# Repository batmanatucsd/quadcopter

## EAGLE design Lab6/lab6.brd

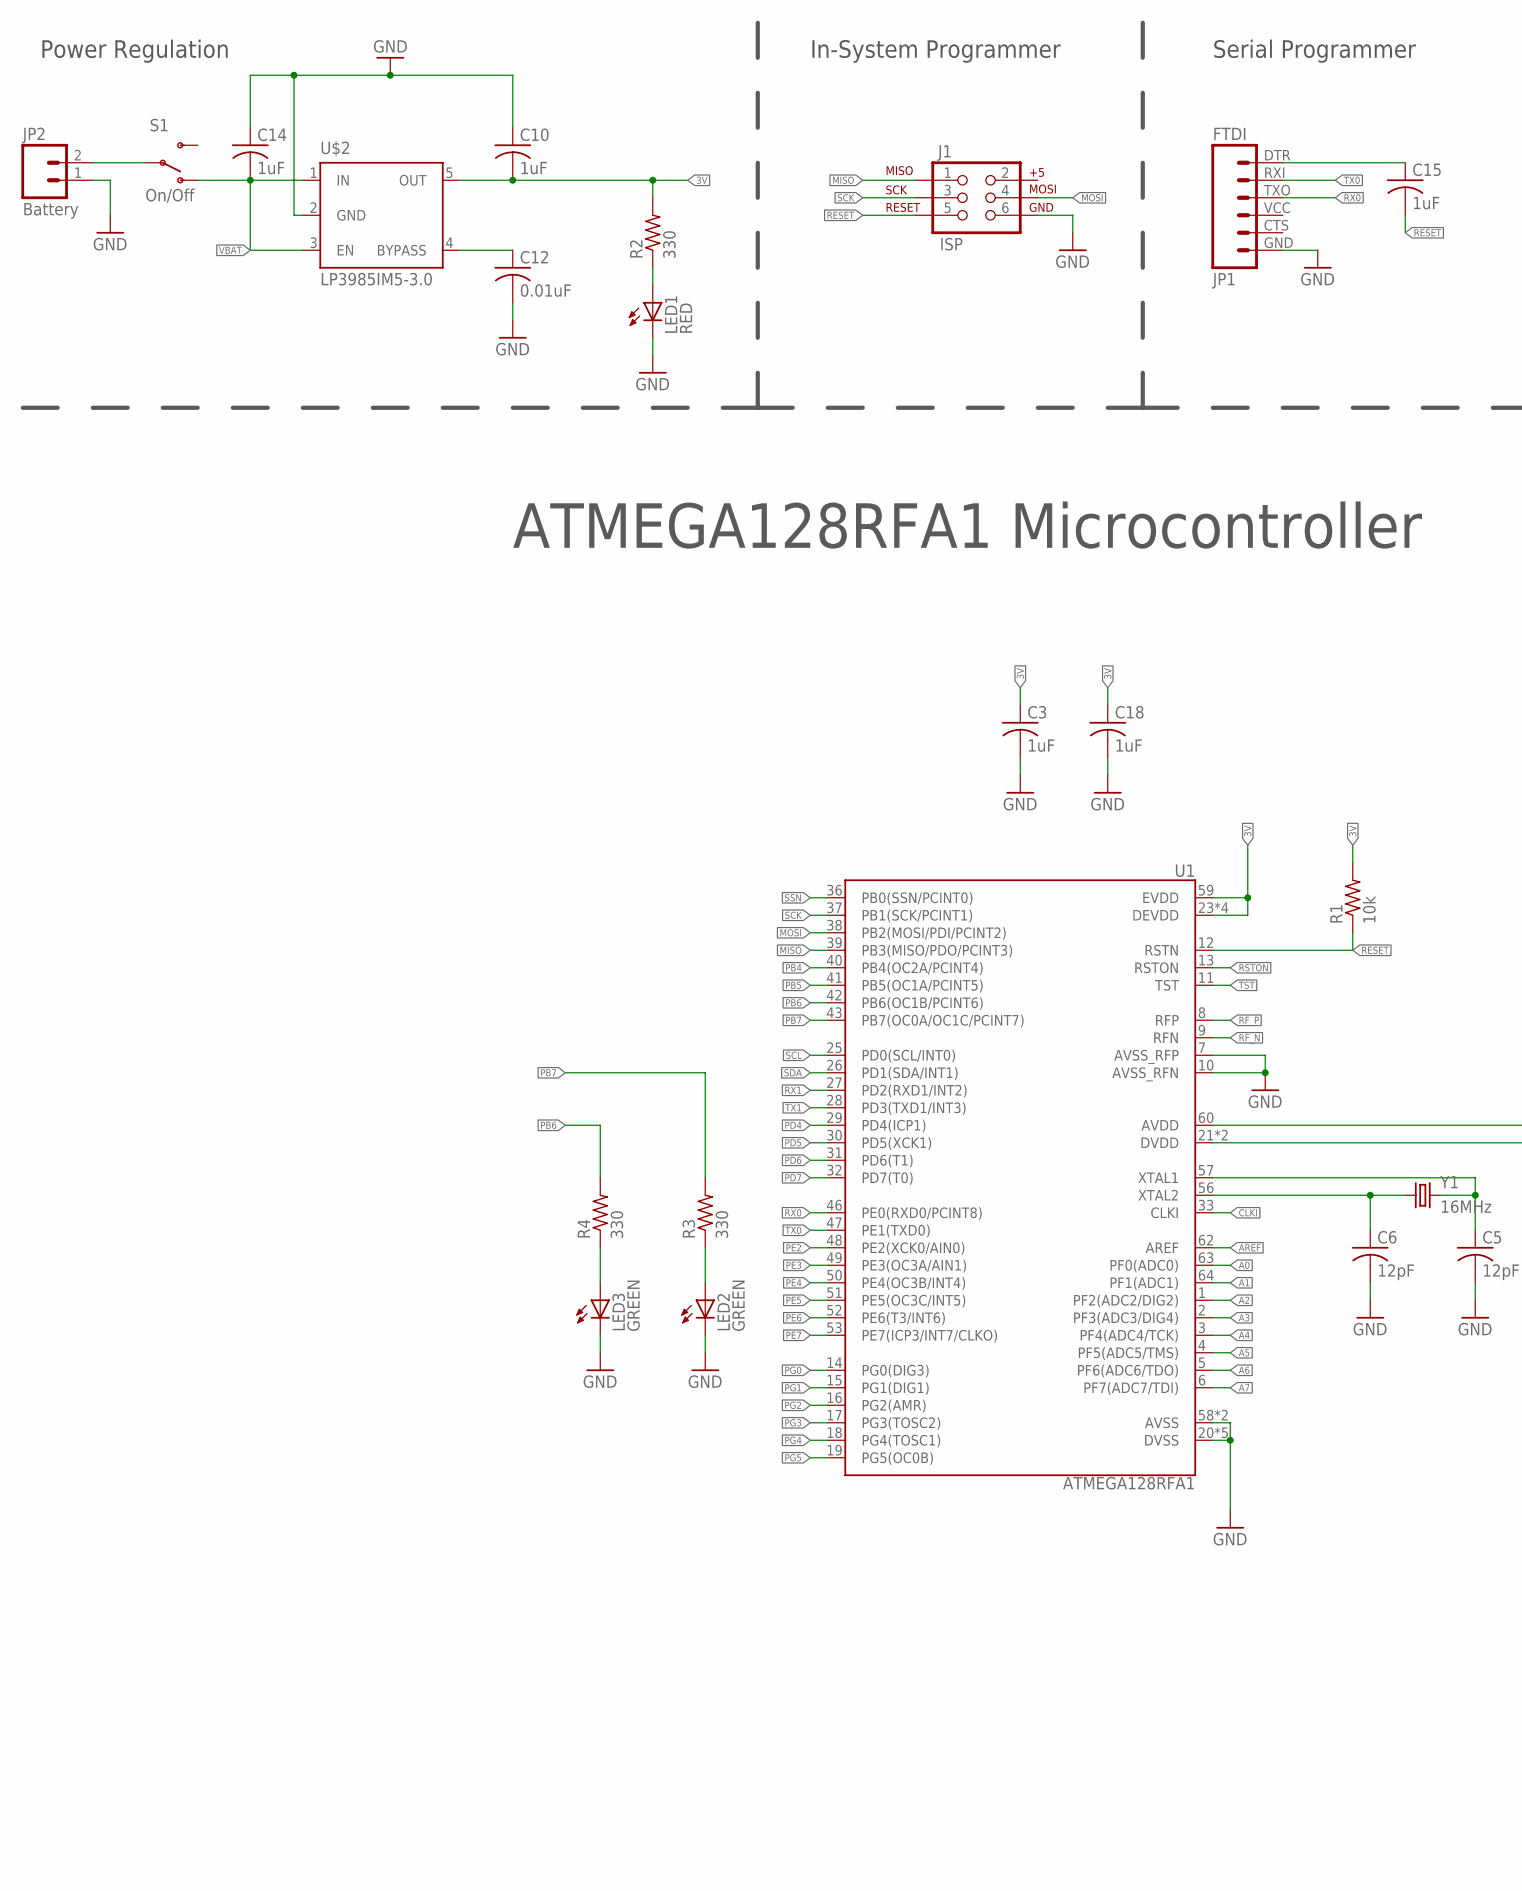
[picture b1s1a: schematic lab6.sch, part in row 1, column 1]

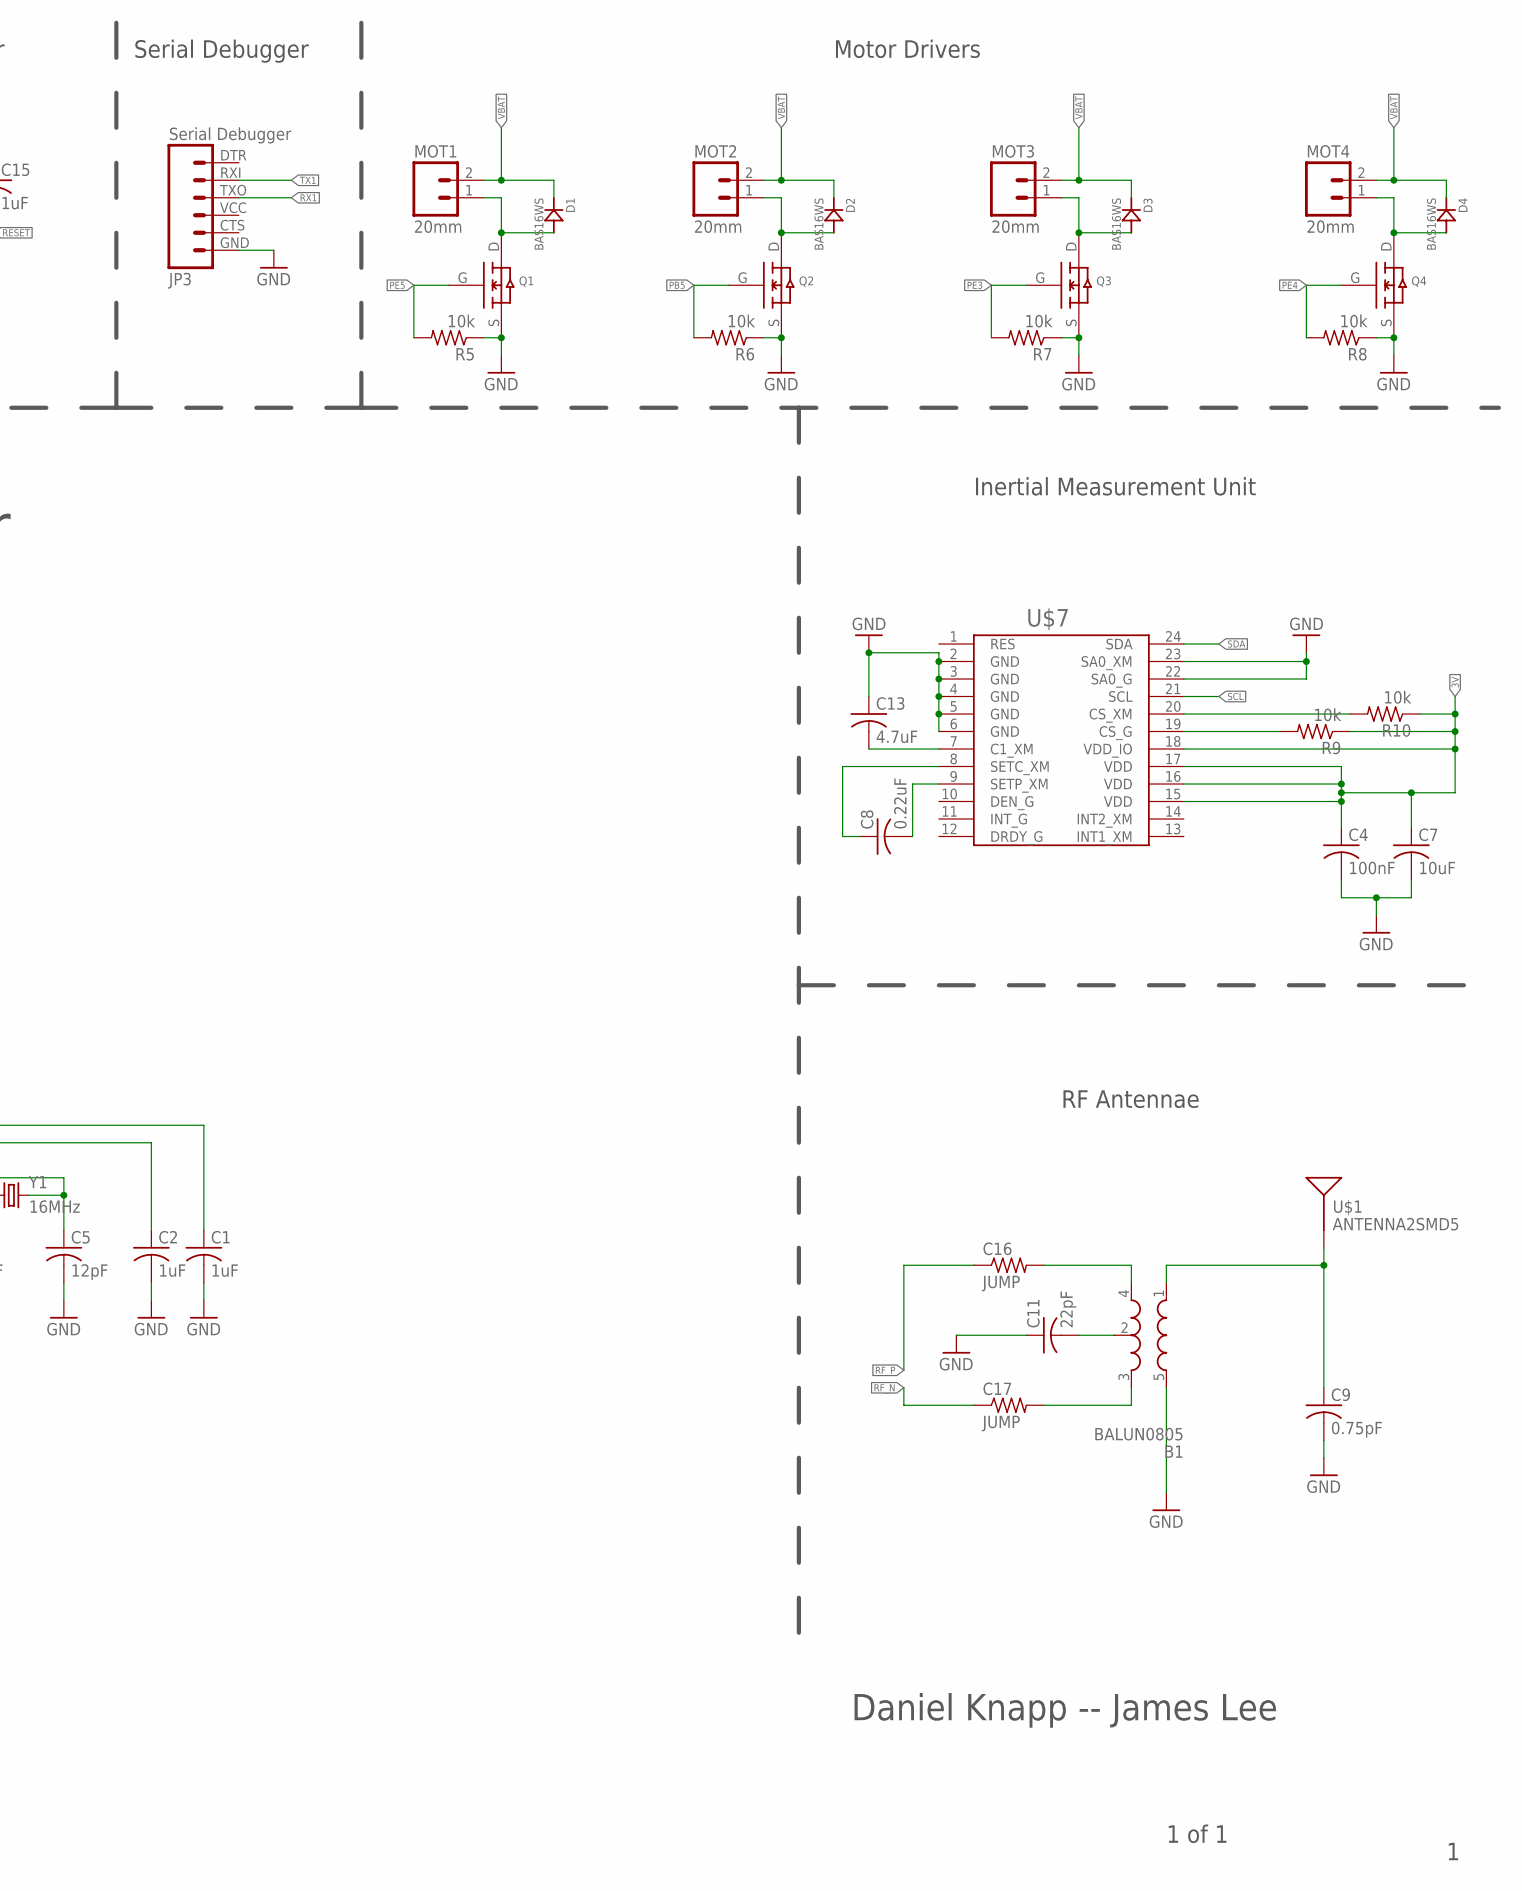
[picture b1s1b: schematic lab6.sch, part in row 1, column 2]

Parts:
B1: BALUN0805; BALUN
C1, C2, C3, C10, C14, C15, C18: 1uF; C0805
C4: 100nF; C0805
C5, C6: 12pF; C0805
C7: 10uF; C0805
C8: 0.22uF; C0805
C9: 0.75pF; C0805
C11: 22pF; C0805
C12: 0.01uF; C0805
C13: 4.7uF; C0805
C16, C17: JUMP; R0805
D1, D2, D3, D4: BAS16WS
J1: ISP; 2X3-NS
JP1: FTDI; FTDI_BASIC
JP2: Battery; 1X02
JP3: Serial Debugger; FTDI_BASIC
LED1: RED; CHIP-LED0805
LED2, LED3: GREEN; CHIP-LED0805
MOT1, MOT2, MOT3, MOT4: 20mm; 1X02
Q1, Q2, Q3, Q4: SI2302CDS
R1, R5, R6, R7, R8, R9, R10: 10k; R0805
R2, R3, R4: 330; R0805
S1: On/Off; SWITCH-SPDT
U1: ATMEGA128RFA1; QFN-64
U$1: ANTENNA2SMD5; ANTENNA-CHIP5
U$2: LP3985IM5-3.0; SOT23-DBV
U$7: LSM9DS0
Y1: 16MHz; CRYSTAL-SMD-5X3

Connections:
3V: C3.1, C4.1, C7.1, C10.2, C18.1, R1.2, R2.2, R9.1, R10.1, U1.23 (DEVDD), U1.34 (DEVDD), U1.44 (DEVDD), U1.54 (DEVDD), U1.59 (EVDD), U$2.5 (OUT), U$7.15 (VDD), U$7.16 (VDD), U$7.17 (VDD), U$7.18 (VDD_IO)
A0: U1.63 (PF0(ADC0))
A1: U1.64 (PF1(ADC1))
A2: U1.1 (PF2(ADC2/DIG2))
A3: U1.2 (PF3(ADC3/DIG4))
A4: U1.3 (PF4(ADC4/TCK))
A5: U1.4 (PF5(ADC5/TMS))
A6: U1.5 (PF6(ADC6/TDO))
A7: U1.6 (PF7(ADC7/TDI))
AREF: U1.62 (AREF)
CLKI: U1.33 (CLKI)
GND: B1.5 (GND), C1.2, C2.2, C3.2, C4.2, C5.2, C6.2, C7.2, C9.2, C10.1, C11.1, C12.2, C13.1, C14.1, C18.2, J1.6, JP1.GND (6), JP2.1, JP3.GND (6), LED1.C, LED2.C, LED3.C, Q1.S, Q2.S, Q3.S, Q4.S, R5.1, R6.1, R7.1, R8.1, U1.7 (AVSS_RFP), U1.10 (AVSS_RFN), U1.20 (DVSS), U1.24 (DVSS), U1.35 (DVSS), U1.45 (DVSS), U1.55 (DVSS), U1.58 (AVSS), U1.61 (AVSS), U$2.2 (GND), U$7.2 (GND), U$7.3 (GND), U$7.4 (GND), U$7.5 (GND), U$7.6 (GND), U$7.22 (SA0_G), U$7.23 (SA0_XM)
MISO: J1.1, U1.39 (PB3(MISO/PDO/PCINT3))
MOSI: J1.4, U1.38 (PB2(MOSI/PDI/PCINT2))
unnamed: C12.1, U$2.4 (BYPASS)
unnamed: C15.1, JP1.DTR (1)
unnamed: LED1.A, R2.1
unnamed: C5.1, U1.57 (XTAL1), Y1.3 (2)
unnamed: JP2.2, S1.2
unnamed: C6.1, U1.56 (XTAL2), Y1.1
unnamed: C2.1, U1.21 (DVDD), U1.22 (DVDD)
unnamed: C1.1, U1.60 (AVDD)
unnamed: B1.3 (OUT2), C17.2
unnamed: B1.2 (GND), C11.2
unnamed: B1.4 (OUT1), C16.2
unnamed: B1.1 (IN), C9.1, U$1.FEED
unnamed: LED3.A, R4.1
unnamed: LED2.A, R3.1
unnamed: D1.P$2, MOT1.1, Q1.D
unnamed: D2.P$2, MOT2.1, Q2.D
unnamed: D3.P$2, MOT3.1, Q3.D
unnamed: D4.P$2, MOT4.1, Q4.D
unnamed: C8.1, U$7.8 (SETC_XM)
unnamed: C8.2, U$7.9 (SETP_XM)
unnamed: C13.2, U$7.7 (C1_XM)
unnamed: R9.2, U$7.19 (CS_G)
unnamed: R10.2, U$7.20 (CS_XM)
PB4: U1.40 (PB4(OC2A/PCINT4))
PB5: Q2.G, R6.2, U1.41 (PB5(OC1A/PCINT5))
PB6: R4.2, U1.42 (PB6(OC1B/PCINT6))
PB7: R3.2, U1.43 (PB7(OC0A/OC1C/PCINT7))
PD4: U1.29 (PD4(ICP1))
PD5: U1.30 (PD5(XCK1))
PD6: U1.31 (PD6(T1))
PD7: U1.32 (PD7(T0))
PE2: U1.48 (PE2(XCK0/AIN0))
PE3: Q3.G, R7.2, U1.49 (PE3(OC3A/AIN1))
PE4: Q4.G, R8.2, U1.50 (PE4(OC3B/INT4))
PE5: Q1.G, R5.2, U1.51 (PE5(OC3C/INT5))
PE6: U1.52 (PE6(T3/INT6))
PE7: U1.53 (PE7(ICP3/INT7/CLKO))
PG0: U1.14 (PG0(DIG3))
PG1: U1.15 (PG1(DIG1))
PG2: U1.16 (PG2(AMR))
PG3: U1.17 (PG3(TOSC2))
PG4: U1.18 (PG4(TOSC1))
PG5: U1.19 (PG5(OC0B))
RESET: C15.2, J1.5, R1.1, U1.12 (RSTN)
RF_N: C17.1, U1.9 (RFN)
RF_P: C16.1, U1.8 (RFP)
RSTON: U1.13 (RSTON)
RX0: JP1.TXO (3), U1.46 (PE0(RXD0/PCINT8))
RX1: JP3.TXO (3), U1.27 (PD2(RXD1/INT2))
SCK: J1.3, U1.37 (PB1(SCK/PCINT1))
SCL: U1.25 (PD0(SCL/INT0)), U$7.21 (SCL)
SDA: U1.26 (PD1(SDA/INT1)), U$7.24 (SDA)
SSN: U1.36 (PB0(SSN/PCINT0))
TST: U1.11 (TST)
TX0: JP1.RXI (2), U1.47 (PE1(TXD0))
TX1: JP3.RXI (2), U1.28 (PD3(TXD1/INT3))
VBAT: C14.2, D1.P$1, D2.P$1, D3.P$1, D4.P$1, MOT1.2, MOT2.2, MOT3.2, MOT4.2, S1.1 (O), U$2.1 (IN), U$2.3 (EN)

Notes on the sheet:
Power Regulation
In-System Programmer
Serial Programmer
Serial Debugger
Motor Drivers
Inertial Measurement Unit
Daniel Knapp -- James Lee
1 of 1
ATMEGA128RFA1 Microcontroller
RF Antennae

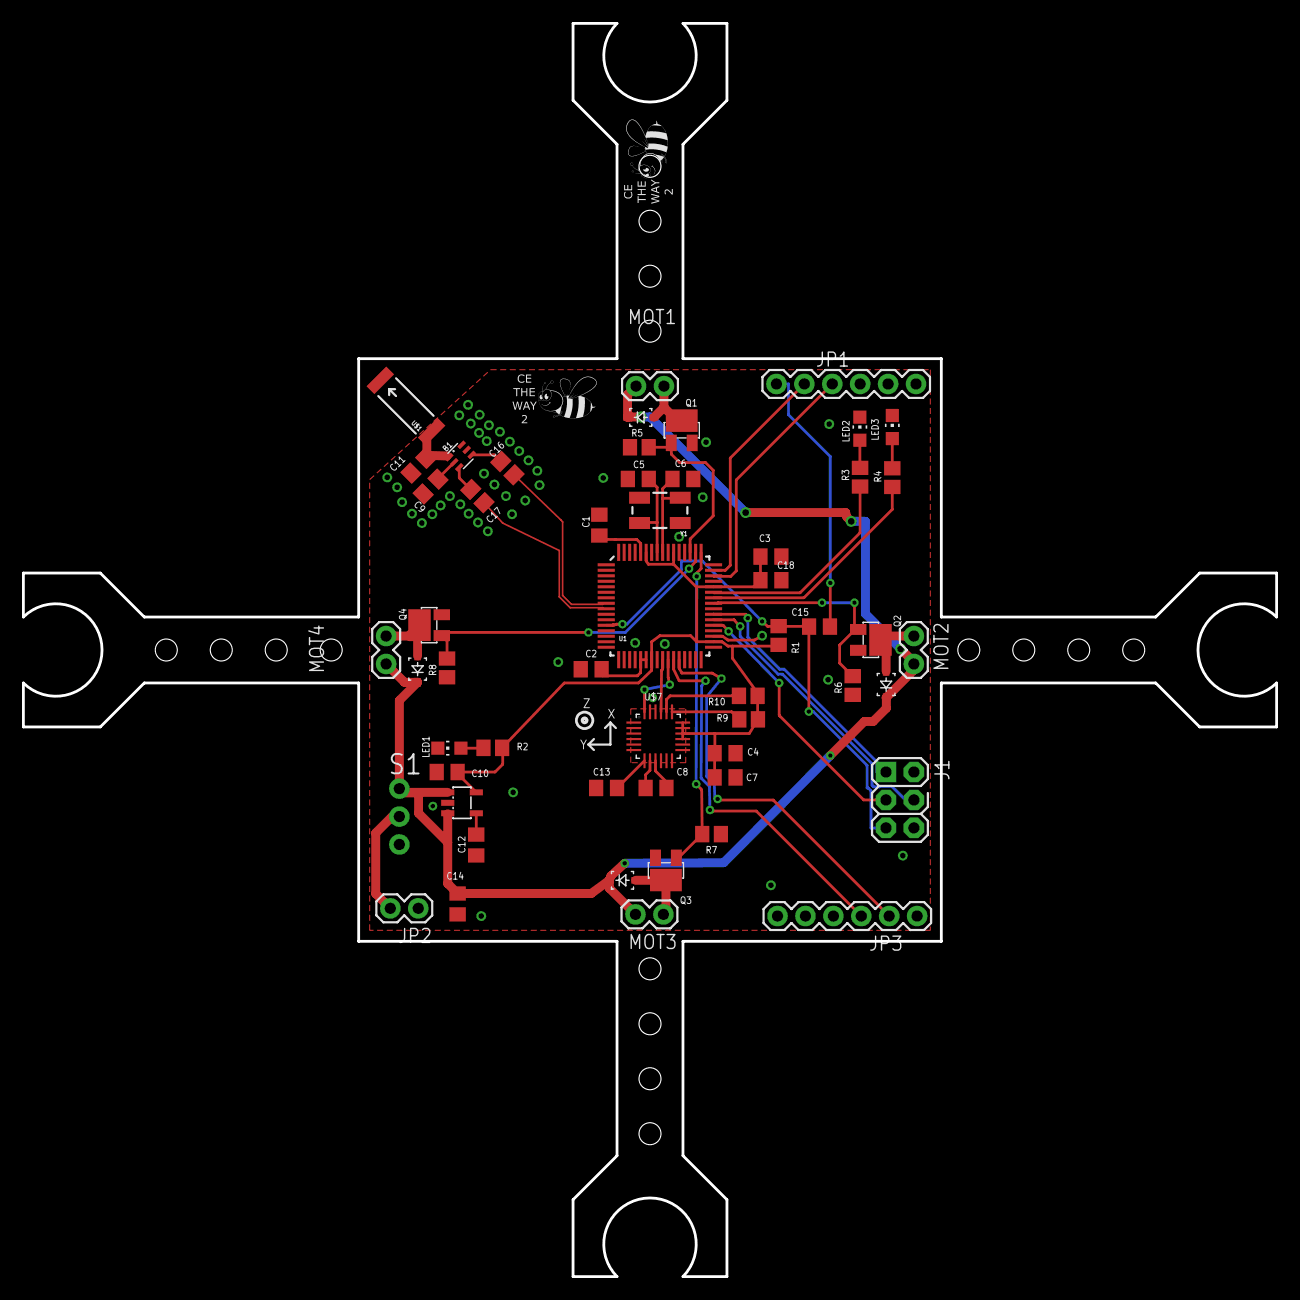
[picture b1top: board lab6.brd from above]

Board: 2 copper layers, 114.0 x 114.0 mm, 56 parts (0 on the bottom side), 44 nets.

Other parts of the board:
U$3, U$4: BEE_LOGO

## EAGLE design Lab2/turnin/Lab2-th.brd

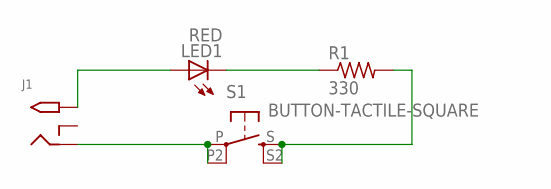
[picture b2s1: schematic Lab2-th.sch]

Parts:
J1: 2.1MMJACKTHM; PJ-102A
LED1: RED; LED5MM
R1: 330; RESAD1160W55L680D260_HS
S1: BUTTON-TACTILE-SQUARE; BUTTON-TACTILE-SQUARE-ADAFRUIT1010

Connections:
unnamed: LED1.K (C), R1.1
unnamed: R1.2, S1.S, S1.S2 (S1)
unnamed: J1.RING, S1.P, S1.P2 (P1)
unnamed: J1.TIP, LED1.A

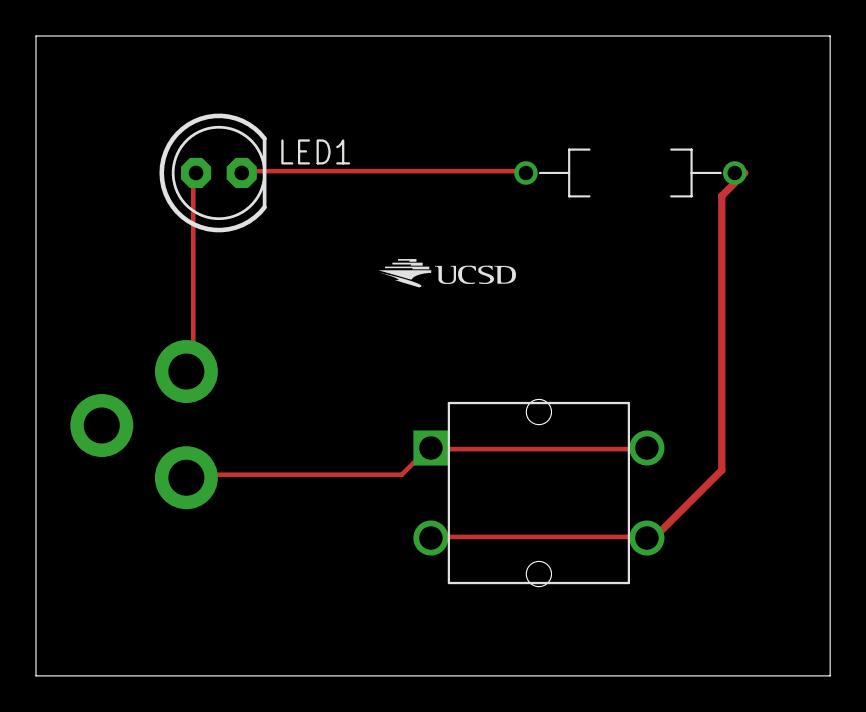
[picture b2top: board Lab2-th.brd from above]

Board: 2 copper layers, 44.1 x 35.5 mm, 5 parts (1 on the bottom side), 4 nets.

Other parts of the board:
U$1: UCSD_LOGO

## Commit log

2015-04-10 added Lab2 and Lab3
2015-04-10 deleted all the files that are not for turn in for lab2 report
2015-04-10 turn in for Lab2 - James Lee A11518245
2015-04-10 removed the readme file
2015-04-10 moved some files
2015-04-10 Lab3 Report - James, Kirt
2015-04-21 added Lab5
2015-04-21 changed the name to lab 5
2015-04-21 Added Daniel's Lab 4 library
2015-04-22 added motor schematic
2015-04-22 We think the Lab 5 schematic is done now.
2015-04-24 Revamped the lab 5 schematic
    Cleaned up the schematic a bunch and condensed the libraries into 1
    called lab5_comps.lbr
2015-04-30 Corrected Schematic and some of the board
2015-04-30 added git ignore and removed all the backup files
2015-04-30 added gitignore file
2015-05-01 messed up the board...
2015-05-01 updated ignore file
2015-05-06 working on making the board smaller
2015-05-06 Added Logo
2015-05-06 Removed Pad Beneath MCU
2015-05-06 Removed Pin From MCU Symbol
2015-05-06 finisehd board. but need to add names
2015-05-07 Update The Board Some Component Names
2015-05-07 final board design
2015-05-07 fixed imu gnd plane
2015-05-07 Added Some Restrict Around IMU
2015-05-08 Added a Lab6 folder for Lab 6
    Stop working in lab 5 plz.
2015-05-08 Did stuff
2015-05-12 Newest Gerber Files
2015-05-13 Fixed What Swanson Wanted
2015-05-13 Fixed Motor Wire Through Antenna Wires
2015-05-13 Added Zip Of Cam Files
2015-05-16 Created BOM.csv
